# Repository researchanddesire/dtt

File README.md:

# DT Trainer

<p align="center">
  
</p>

<p align="center">
  <a href="https://www.researchanddesire.com/products/deepthroat-trainer"><b>Get the Deepthroat Trainer</b></a><br>
  Black Friday: use code <code>BLACK_FRIDAY_2026</code> at checkout.
</p>

ESP32 firmware and hardware for the V1 (4 MiB) and V2 (16 MiB) DT Trainer.
Firmware: MPL-2.0. Hardware: CERN-OHL-S v2. User guides:
[CC BY-SA 4.0](https://github.com/researchanddesire/simple-docs/blob/main/LICENSE).

## Hardware

- [FreeCAD assembly](hardware/cad/)
- [KiCad PCB](hardware/pcb/kicad-rev4/217A_dttrainer_rev4/)
- [PCB production files](hardware/pcb/production/)
- [Assembly guide](assembly-docs/assembly-guide.mdx)

## Documentation

[User guides](docs/) mirror [Simple Docs](https://github.com/researchanddesire/simple-docs/tree/main/content/dtt).
The daily sync can also run with `python software/scripts/sync_user_docs.py`.
[Firmware and engineering docs](developer-docs/docs/) are maintained here.

## Build

Software lives in [`software/`](software/): the PlatformIO firmware project in
[`software/firmware/`](software/firmware/), development and CI tooling in
[`software/scripts/`](software/scripts/), and local development settings in
[`software/dev/`](software/dev/). Use Python 3.12 and PlatformIO Core 6.2.0:

```sh
python -m pip install platformio==6.2.0
cd software/firmware
pio run -e staging-v1 -e staging-v2 -e production-v1 -e production-v2
```

Select the environment matching the board. Builds do not flash a device.
Development builds (`development`, `development-v1`, `development-v2`) target a
local dashboard on port 3000 (or the origin in the ignored
`software/dev/local.settings.json`). Release builds read the dashboard API credential
from the `RAD_PUBLIC_KEY` environment variable; without it they use the
`DEV_KEY_123` placeholder. Never commit the credential. Flash explicitly:

```sh
pio run -e development-v1 -t upload
```

Keep deployed partition offsets and stored device identity intact.
See [AGENTS.md](AGENTS.md), [software/firmware/README.md](software/firmware/README.md), and
[CI](.github/workflows/) for checks.

See [CONTRIBUTING.md](CONTRIBUTING.md) to contribute.

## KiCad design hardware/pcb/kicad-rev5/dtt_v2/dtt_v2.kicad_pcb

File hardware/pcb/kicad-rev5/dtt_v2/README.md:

# DTT v2 PCB (rev 5)

ESP32-S3 board for the DTT v2: 2.0 in touch screen, VL53L4CD time-of-flight
sensor, LSM6DSO + LIS3MDL 9DOF IMU, side PH6 accessory port. No LEDs, button
or headphone jack. 38 x 64 mm (rev 4 is 44 x 92 mm) with four M2 case-screw
holes. LCSC numbers on every part except the screen connector and the PH6
header. The [case and cradle](../../../cad/dtt-v2/) are built around it.

Status: routed, KiCad 9 DRC clean. Not yet reviewed or fabbed.

| Back | Front |
| --- | --- |
|  |  |

## Source

`build_dtt_v2.py` generates the schematic, libraries, project and placed board
from one netlist; `route_dtt_v2.py` routes it (about an hour). Both overwrite
the board, so once it is hand-edited in KiCad, stop running them.

## PH6 accessory port

| Pin | Signal |
| --- | --- |
| 1 | GND |
| 2 | VSYS (0.5 A PTC) |
| 3 | OUT1, 3.3 V high-side |
| 4 | OUT2, 3.3 V high-side |
| 5 | I2C SDA |
| 6 | I2C SCL |

Existing 3.5 mm accessories use an adapter: tip GND, ring 1 OUT1, ring 2 OUT2.

## I2C addresses

Touch 0x15, ToF 0x29, IMU 0x6A, magnetometer 0x1C.

## Screen

Bare 2.0 in 240x320 IPS panel with CST816D touch, the one inside Waveshare's
"2inch Capacitive Touch LCD" module. 21-pin 0.5 mm FPC, pin order from that
module's schematic:

| Pin | Signal | | Pin | Signal |
| --- | --- | --- | --- | --- |
| 1 | GND | | 12 | RS (DC) |
| 2 | LEDK | | 13 | CS |
| 3 | LEDA | | 14 | GND |
| 4 | GND | | 15 | TP_VDD (3.3 V) |
| 5, 6 | VCC (3.3 V) | | 16 | TP_RESET |
| 7 | GND | | 17 | TP_INT |
| 8 | RESET | | 18 | TP_SDA |
| 9 | SCL (SPI clock) | | 19 | TP_SCL |
| 10 | TE | | 20, 21 | GND |
| 11 | SDA (MOSI) | | | |

## Open items

- Check on a panel sample: LEDA/LEDK order, FPC contact side (J3 is
  top-contact for now), glass outline (36 x 52 mm assumed).
- Backlight is 3.3 V through 10 R, so not full brightness.
- Battery: 702035 (400 mAh). R3 is 3.3k, so the TP4054 charges at about 300 mA (0.76C).
- SW1 reuses the rev 4 footprint with its tight locating holes.
- J4 is the surface-mount S6B-PH-SM4-TB (no pins through the front under the
  glass); confirm its LCSC number before ordering.
- The ToF sits at the bottom right of the front face, beside the screen FPC,
  looking through a window in the case bezel.

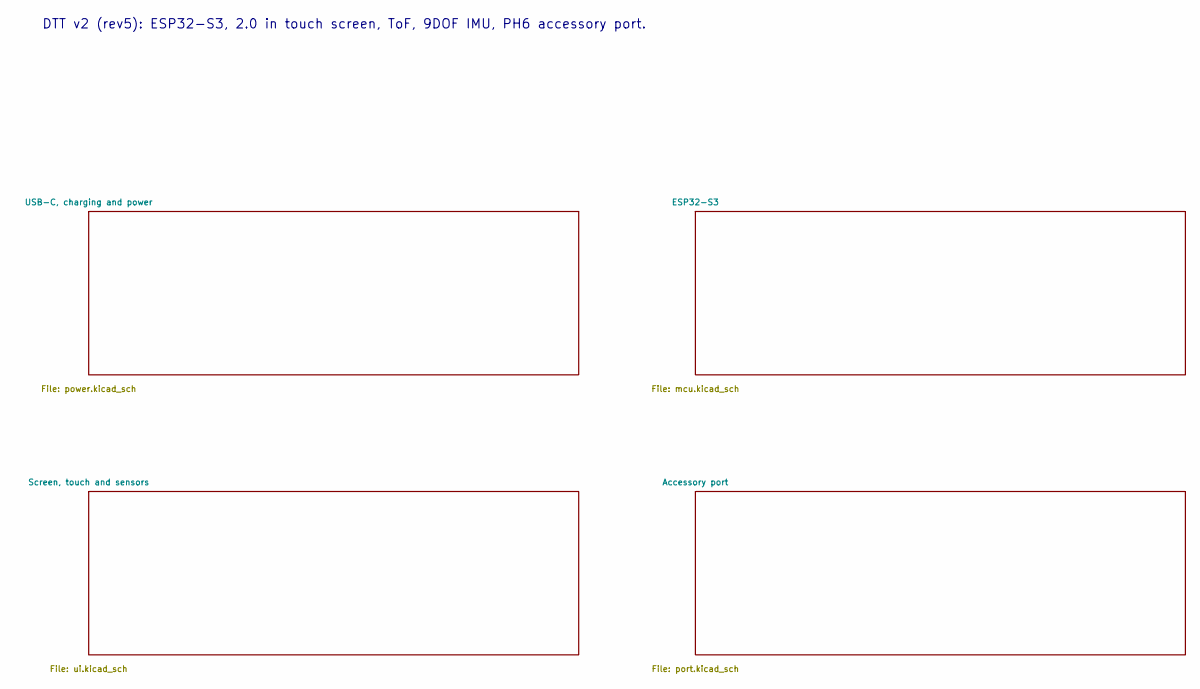
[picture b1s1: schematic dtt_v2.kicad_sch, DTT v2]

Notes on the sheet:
DTT v2 (rev5): ESP32-S3, 2.0 in touch screen, ToF, 9DOF IMU, PH6 accessory port.

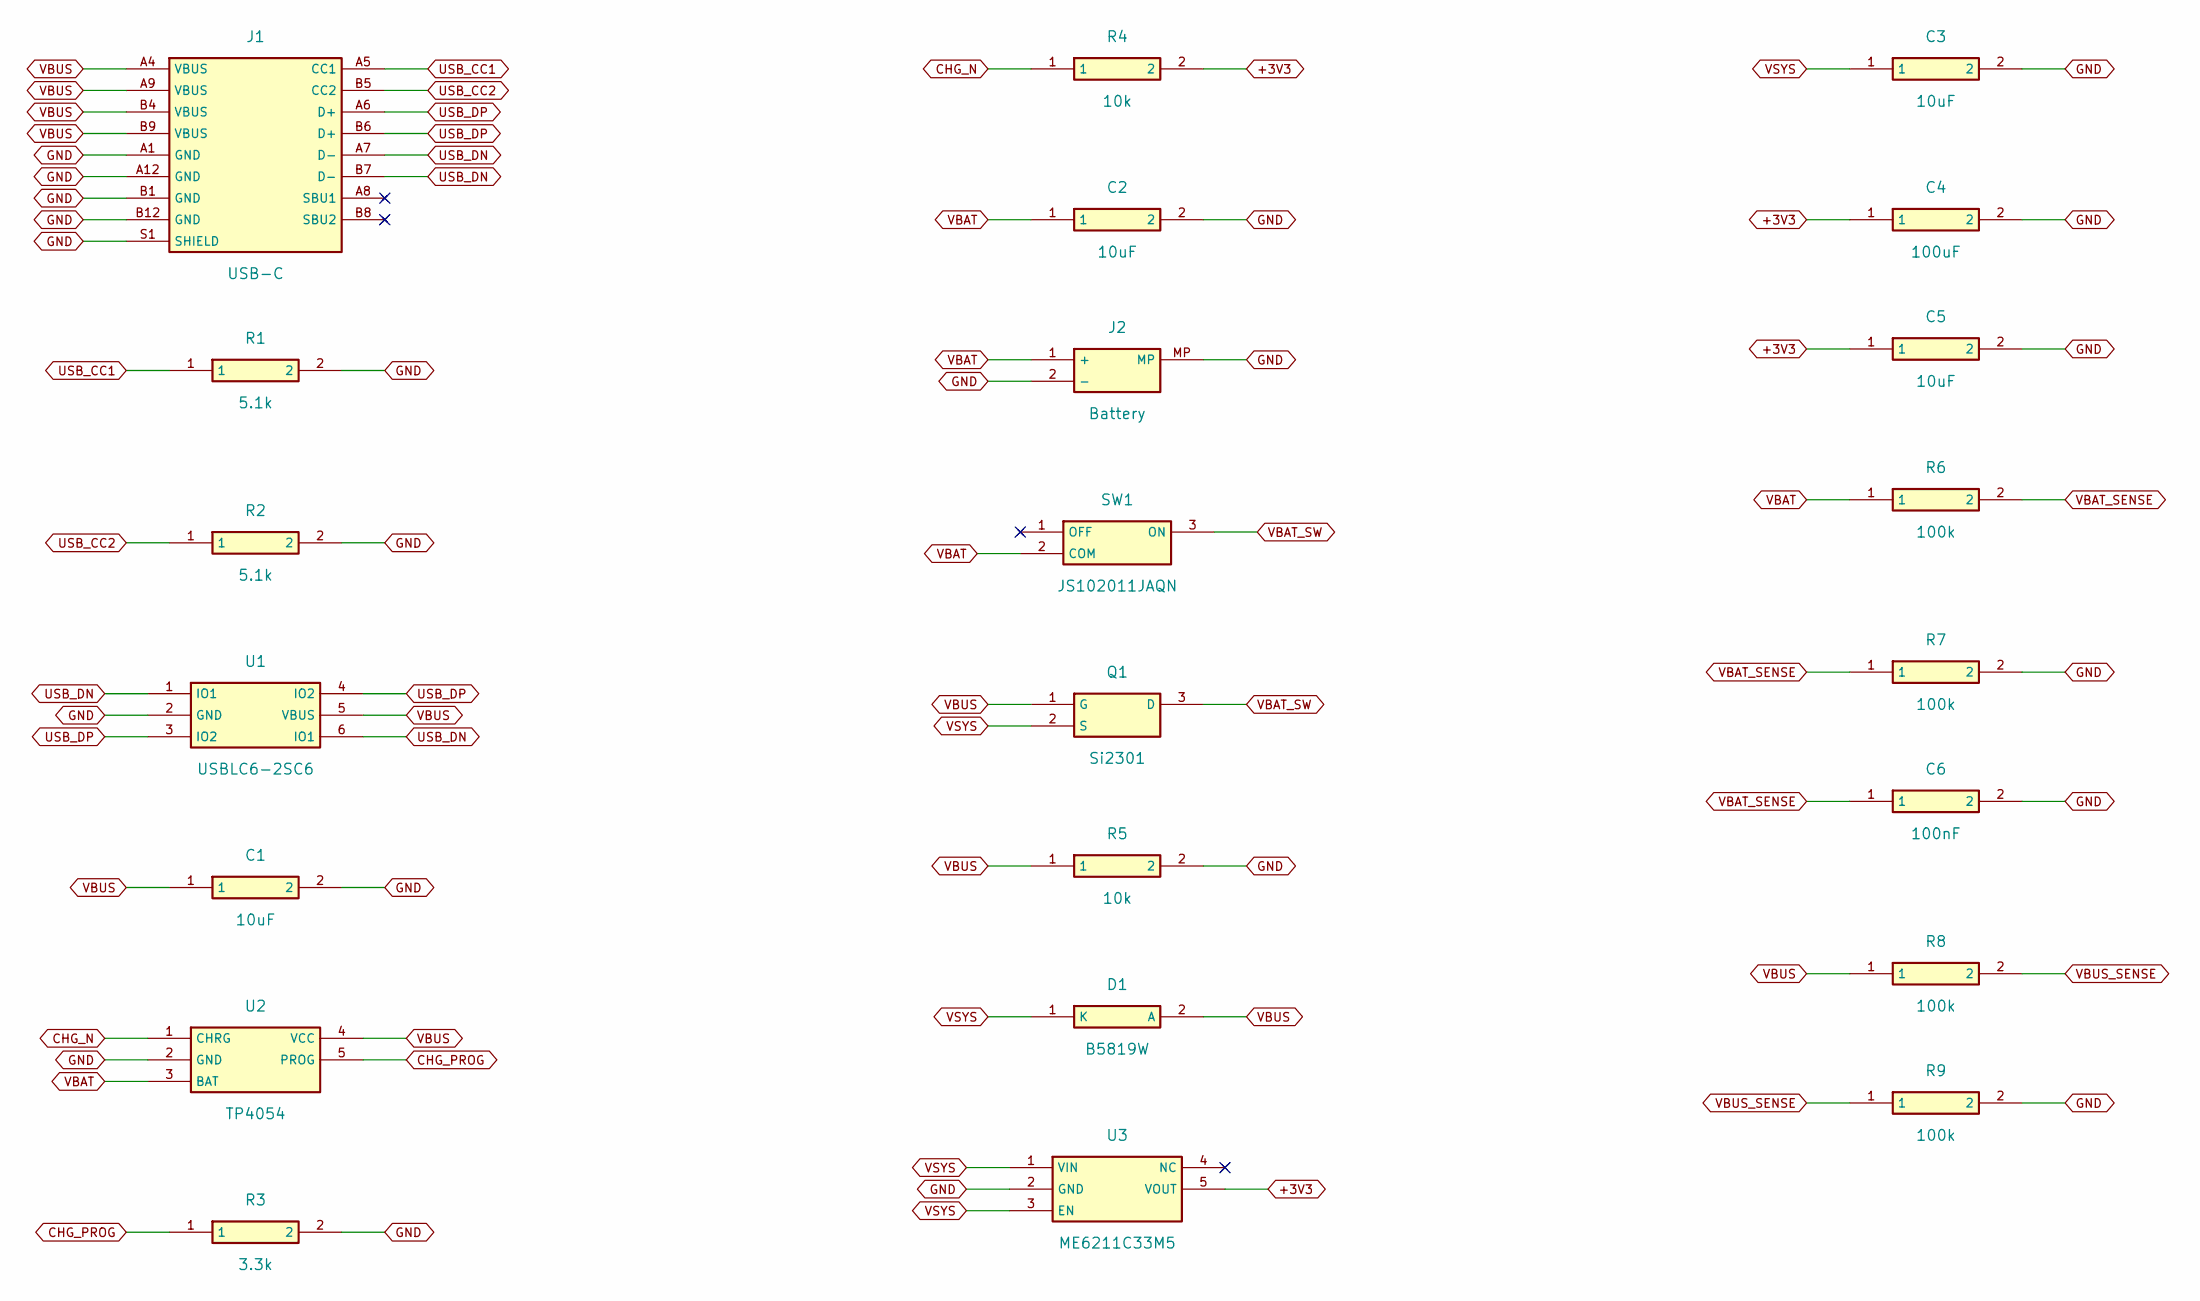
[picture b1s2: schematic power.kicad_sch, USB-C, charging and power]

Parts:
C1, C2, C3, C5: 10uF; C_0805_2012Metric; LCSC C89827
C4: 100uF; C_1206_3216Metric; LCSC C7432784
C6: 100nF; C_0402_1005Metric; LCSC C56392
D1: B5819W; D_SOD-123; LCSC C22463588
J1: USB-C; USB_C_Receptacle_HRO_TYPE-C-31-M-12; LCSC C165948
J2: Battery; JST_PH_S2B-PH-SM4-TB_1x02-1MP_P2.00mm_Horizontal; LCSC C295747
Q1: Si2301; SOT-23; LCSC C727151
R1, R2: 5.1k; R_0402_1005Metric; LCSC C25905
R3: 3.3k; R_0402_1005Metric; LCSC C25890
R4, R5: 10k; R_0402_1005Metric; LCSC C25744
R6, R7, R8, R9: 100k; R_0402_1005Metric; LCSC C25741
SW1: JS102011JAQN; SW_SPDT_JS102011JAQN; LCSC C221658
U1: USBLC6-2SC6; SOT-23-6; LCSC C7519
U2: TP4054; SOT-23-5; LCSC C32574
U3: ME6211C33M5; SOT-23-5; LCSC C82942

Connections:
+3V3: C4.1, C5.1, R4.2, U3.5 (VOUT); also elsewhere on the board
CHG_N: R4.1, U2.1 (CHRG); also elsewhere on the board
CHG_PROG: R3.1, U2.5 (PROG)
GND: C1.2, C2.2, C3.2, C4.2, C5.2, C6.2, J1.A1 (GND), J1.A12 (GND), J1.B1 (GND), J1.B12 (GND), J1.S1 (SHIELD), J2.2 (-), J2.MP, R1.2, R2.2, R3.2, R5.2, R7.2, R9.2, U1.2 (GND), U2.2 (GND), U3.2 (GND); also elsewhere on the board
USB_CC1: J1.A5 (CC1), R1.1
USB_CC2: J1.B5 (CC2), R2.1
USB_DN: J1.A7 (D-), J1.B7 (D-), U1.1 (IO1), U1.6 (IO1); also elsewhere on the board
USB_DP: J1.A6 (D+), J1.B6 (D+), U1.3 (IO2), U1.4 (IO2); also elsewhere on the board
VBAT: C2.1, J2.1 (+), R6.1, SW1.2 (COM), U2.3 (BAT)
VBAT_SENSE: C6.1, R6.2, R7.1; also elsewhere on the board
VBAT_SW: Q1.3 (D), SW1.3 (ON)
VBUS: C1.1, D1.2 (A), J1.A4 (VBUS), J1.A9 (VBUS), J1.B4 (VBUS), J1.B9 (VBUS), Q1.1 (G), R5.1, R8.1, U1.5 (VBUS), U2.4 (VCC)
VBUS_SENSE: R8.2, R9.1; also elsewhere on the board
VSYS: C3.1, D1.1 (K), Q1.2 (S), U3.1 (VIN), U3.3 (EN); also elsewhere on the board

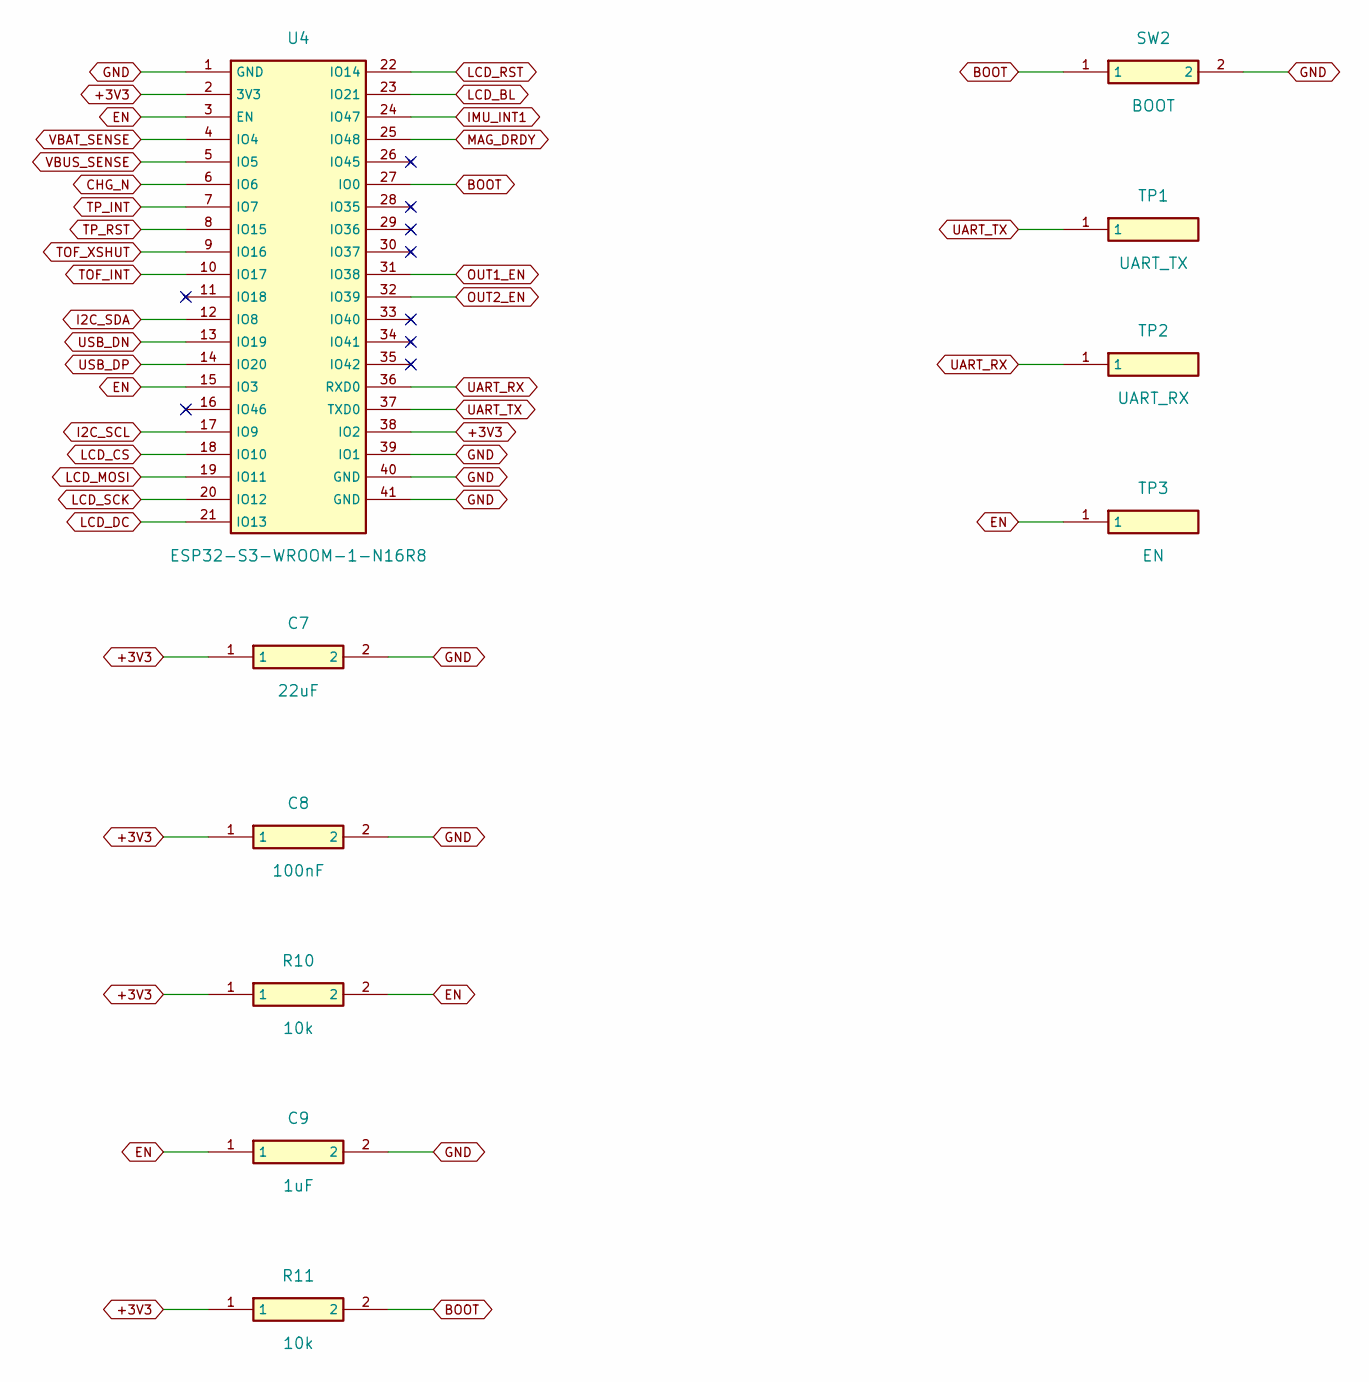
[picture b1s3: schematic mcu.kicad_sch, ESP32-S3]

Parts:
C7: 22uF; C_0805_2012Metric; LCSC TBD
C8: 100nF; C_0402_1005Metric; LCSC C56392
C9: 1uF; C_0402_1005Metric; LCSC C52923
R10, R11: 10k; R_0402_1005Metric; LCSC C25744
SW2: BOOT; SW_Push_1P1T_XKB_TS-1187A; LCSC TBD
TP1: UART_TX; TestPoint_Pad_1.0mm; LCSC TBD
TP2: UART_RX; TestPoint_Pad_1.0mm; LCSC TBD
TP3: EN; TestPoint_Pad_1.0mm; LCSC TBD
U4: ESP32-S3-WROOM-1-N16R8; ESP32-S3-WROOM-1; LCSC C2913202

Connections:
+3V3: C7.1, C8.1, R10.1, R11.1, U4.2 (3V3), U4.38 (IO2); also elsewhere on the board
BOOT: R11.2, SW2.1, U4.27 (IO0)
CHG_N: U4.6 (IO6); also elsewhere on the board
EN: C9.1, R10.2, TP3.1, U4.3 (EN), U4.15 (IO3)
GND: C7.2, C8.2, C9.2, SW2.2, U4.1 (GND), U4.39 (IO1), U4.40 (GND), U4.41 (GND); also elsewhere on the board
I2C_SCL: U4.17 (IO9); also elsewhere on the board
I2C_SDA: U4.12 (IO8); also elsewhere on the board
IMU_INT1: U4.24 (IO47); also elsewhere on the board
LCD_BL: U4.23 (IO21); also elsewhere on the board
LCD_CS: U4.18 (IO10); also elsewhere on the board
LCD_DC: U4.21 (IO13); also elsewhere on the board
LCD_MOSI: U4.19 (IO11); also elsewhere on the board
LCD_RST: U4.22 (IO14); also elsewhere on the board
LCD_SCK: U4.20 (IO12); also elsewhere on the board
LCD_TE: U4.33 (IO40); also elsewhere on the board
MAG_DRDY: U4.25 (IO48); also elsewhere on the board
OUT1_EN: U4.31 (IO38); also elsewhere on the board
OUT2_EN: U4.32 (IO39); also elsewhere on the board
TOF_INT: U4.10 (IO17); also elsewhere on the board
TOF_XSHUT: U4.9 (IO16); also elsewhere on the board
TP_INT: U4.7 (IO7); also elsewhere on the board
TP_RST: U4.8 (IO15); also elsewhere on the board
UART_RX: TP2.1, U4.36 (RXD0)
UART_TX: TP1.1, U4.37 (TXD0)
USB_DN: U4.13 (IO19); also elsewhere on the board
USB_DP: U4.14 (IO20); also elsewhere on the board
VBAT_SENSE: U4.4 (IO4); also elsewhere on the board
VBUS_SENSE: U4.5 (IO5); also elsewhere on the board

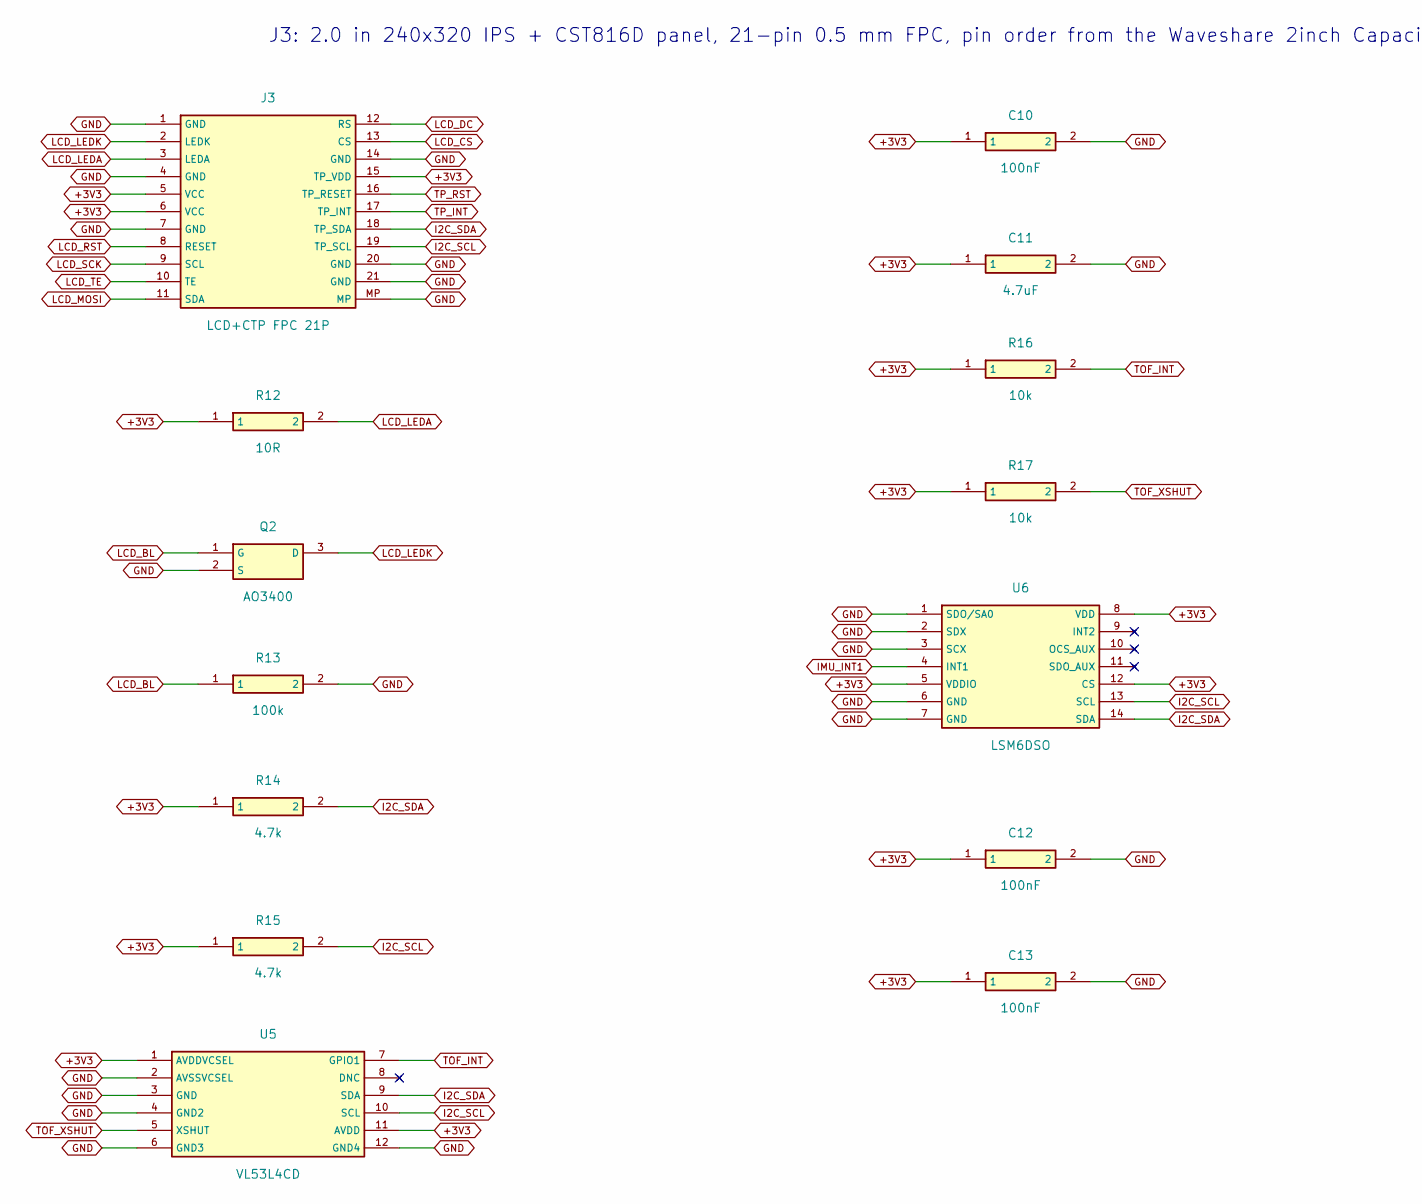
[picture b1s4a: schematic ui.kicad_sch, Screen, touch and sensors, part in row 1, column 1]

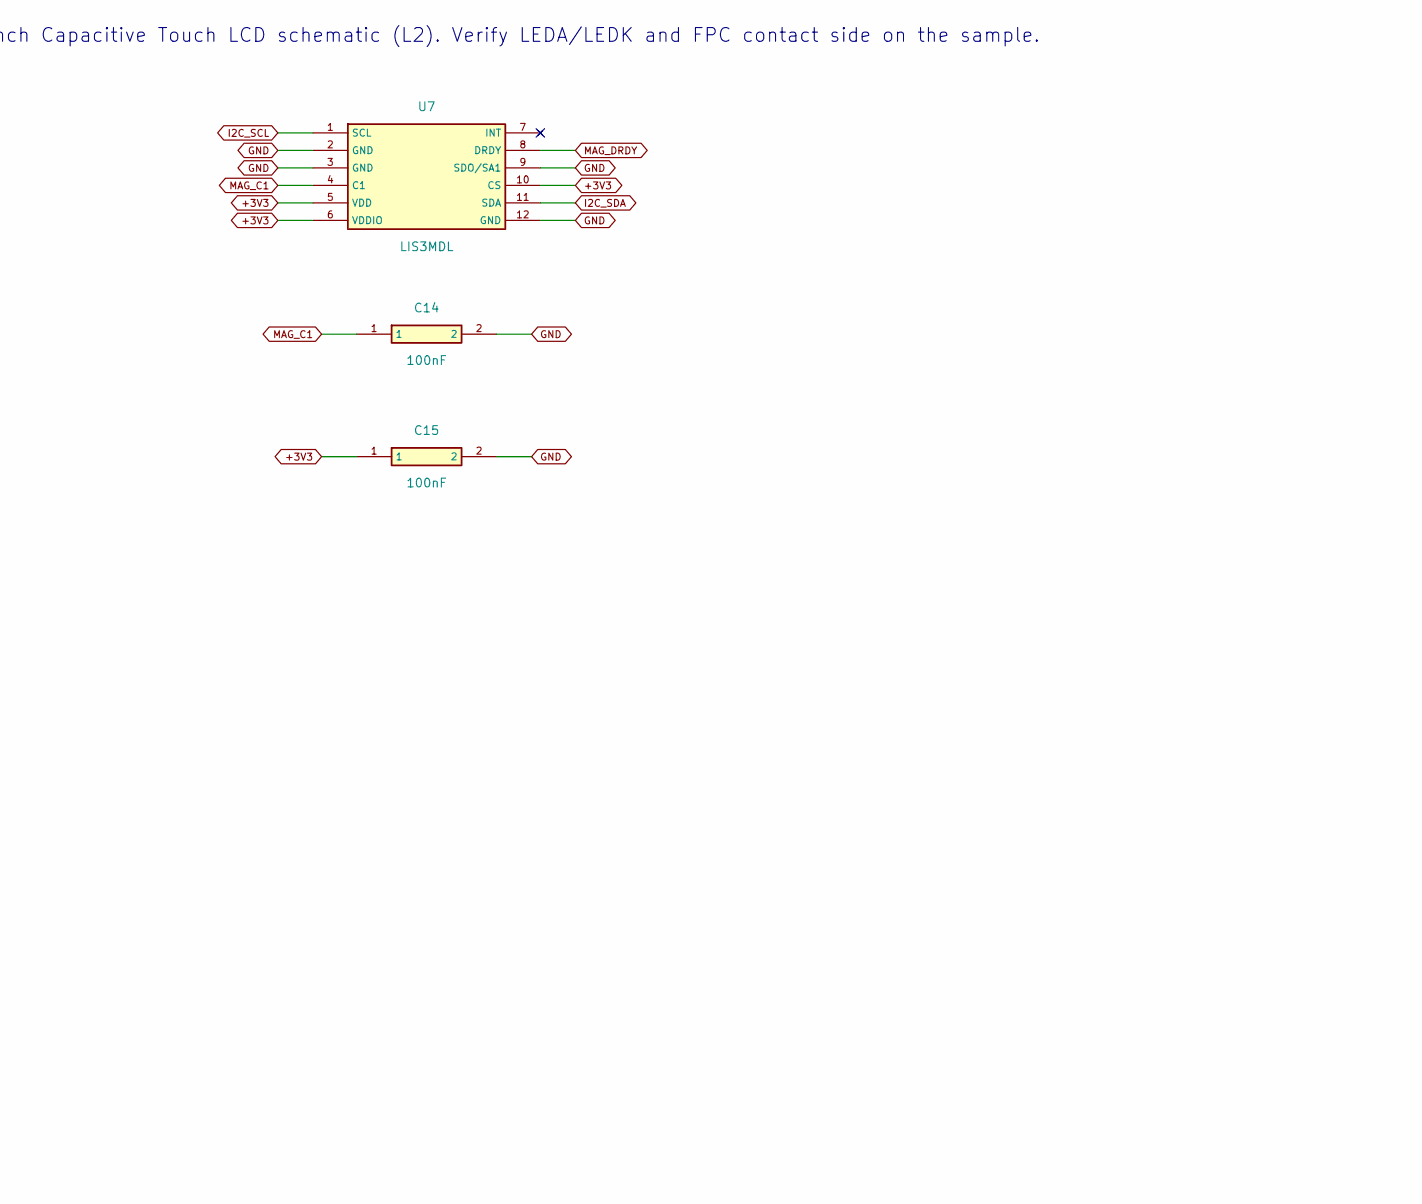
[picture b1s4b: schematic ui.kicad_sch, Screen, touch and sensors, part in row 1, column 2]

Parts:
C10, C12, C13, C14, C15: 100nF; C_0402_1005Metric; LCSC C56392
C11: 4.7uF; C_0402_1005Metric; LCSC C23733
J3: LCD+CTP FPC 21P; TE_2-1734839-1_1x21-1MP_P0.5mm_Horizontal; LCSC TBD
Q2: AO3400; SOT-23; LCSC C2938367
R12: 10R; R_0402_1005Metric; LCSC C25077
R13: 100k; R_0402_1005Metric; LCSC C25741
R14, R15: 4.7k; R_0402_1005Metric; LCSC C25900
R16, R17: 10k; R_0402_1005Metric; LCSC C25744
U5: VL53L4CD; ST_VL53L4CD_LGA-12_4.4x2.4mm; LCSC C3178291
U6: LSM6DSO; ST_LGA-14_2.5x3mm_P0.5mm; LCSC C2655100
U7: LIS3MDL; ST_LGA-12_2x2mm_P0.5mm; LCSC C478483

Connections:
+3V3: C10.1, C11.1, C12.1, C13.1, C15.1, J3.5 (VCC), J3.6 (VCC), J3.15 (TP_VDD), R12.1, R14.1, R15.1, R16.1, R17.1, U5.1 (AVDDVCSEL), U5.11 (AVDD), U6.5 (VDDIO), U6.8 (VDD), U6.12 (CS), U7.5 (VDD), U7.6 (VDDIO), U7.10 (CS); also elsewhere on the board
GND: C10.2, C11.2, C12.2, C13.2, C14.2, C15.2, J3.1 (GND), J3.4 (GND), J3.7 (GND), J3.14 (GND), J3.20 (GND), J3.21 (GND), J3.MP, Q2.2 (S), R13.2, U5.2 (AVSSVCSEL), U5.3 (GND), U5.4 (GND2), U5.6 (GND3), U5.12 (GND4), U6.1 (SDO/SA0), U6.2 (SDX), U6.3 (SCX), U6.6 (GND), U6.7 (GND), U7.2 (GND), U7.3 (GND), U7.9 (SDO/SA1), U7.12 (GND); also elsewhere on the board
I2C_SCL: J3.19 (TP_SCL), R15.2, U5.10 (SCL), U6.13 (SCL), U7.1 (SCL); also elsewhere on the board
I2C_SDA: J3.18 (TP_SDA), R14.2, U5.9 (SDA), U6.14 (SDA), U7.11 (SDA); also elsewhere on the board
IMU_INT1: U6.4 (INT1); also elsewhere on the board
LCD_BL: Q2.1 (G), R13.1; also elsewhere on the board
LCD_CS: J3.13 (CS); also elsewhere on the board
LCD_DC: J3.12 (RS); also elsewhere on the board
LCD_LEDA: J3.3 (LEDA), R12.2
LCD_LEDK: J3.2 (LEDK), Q2.3 (D)
LCD_MOSI: J3.11 (SDA); also elsewhere on the board
LCD_RST: J3.8 (RESET); also elsewhere on the board
LCD_SCK: J3.9 (SCL); also elsewhere on the board
LCD_TE: J3.10 (TE); also elsewhere on the board
MAG_C1: C14.1, U7.4 (C1)
MAG_DRDY: U7.8 (DRDY); also elsewhere on the board
TOF_INT: R16.2, U5.7 (GPIO1); also elsewhere on the board
TOF_XSHUT: R17.2, U5.5 (XSHUT); also elsewhere on the board
TP_INT: J3.17 (TP_INT); also elsewhere on the board
TP_RST: J3.16 (TP_RESET); also elsewhere on the board

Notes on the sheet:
J3: 2.0 in 240x320 IPS + CST816D panel, 21-pin 0.5 mm FPC, pin order from the Waveshare 2inch Capacitive Touch LCD schematic (L2). Verify LEDA/LEDK and FPC contact side on the sample.

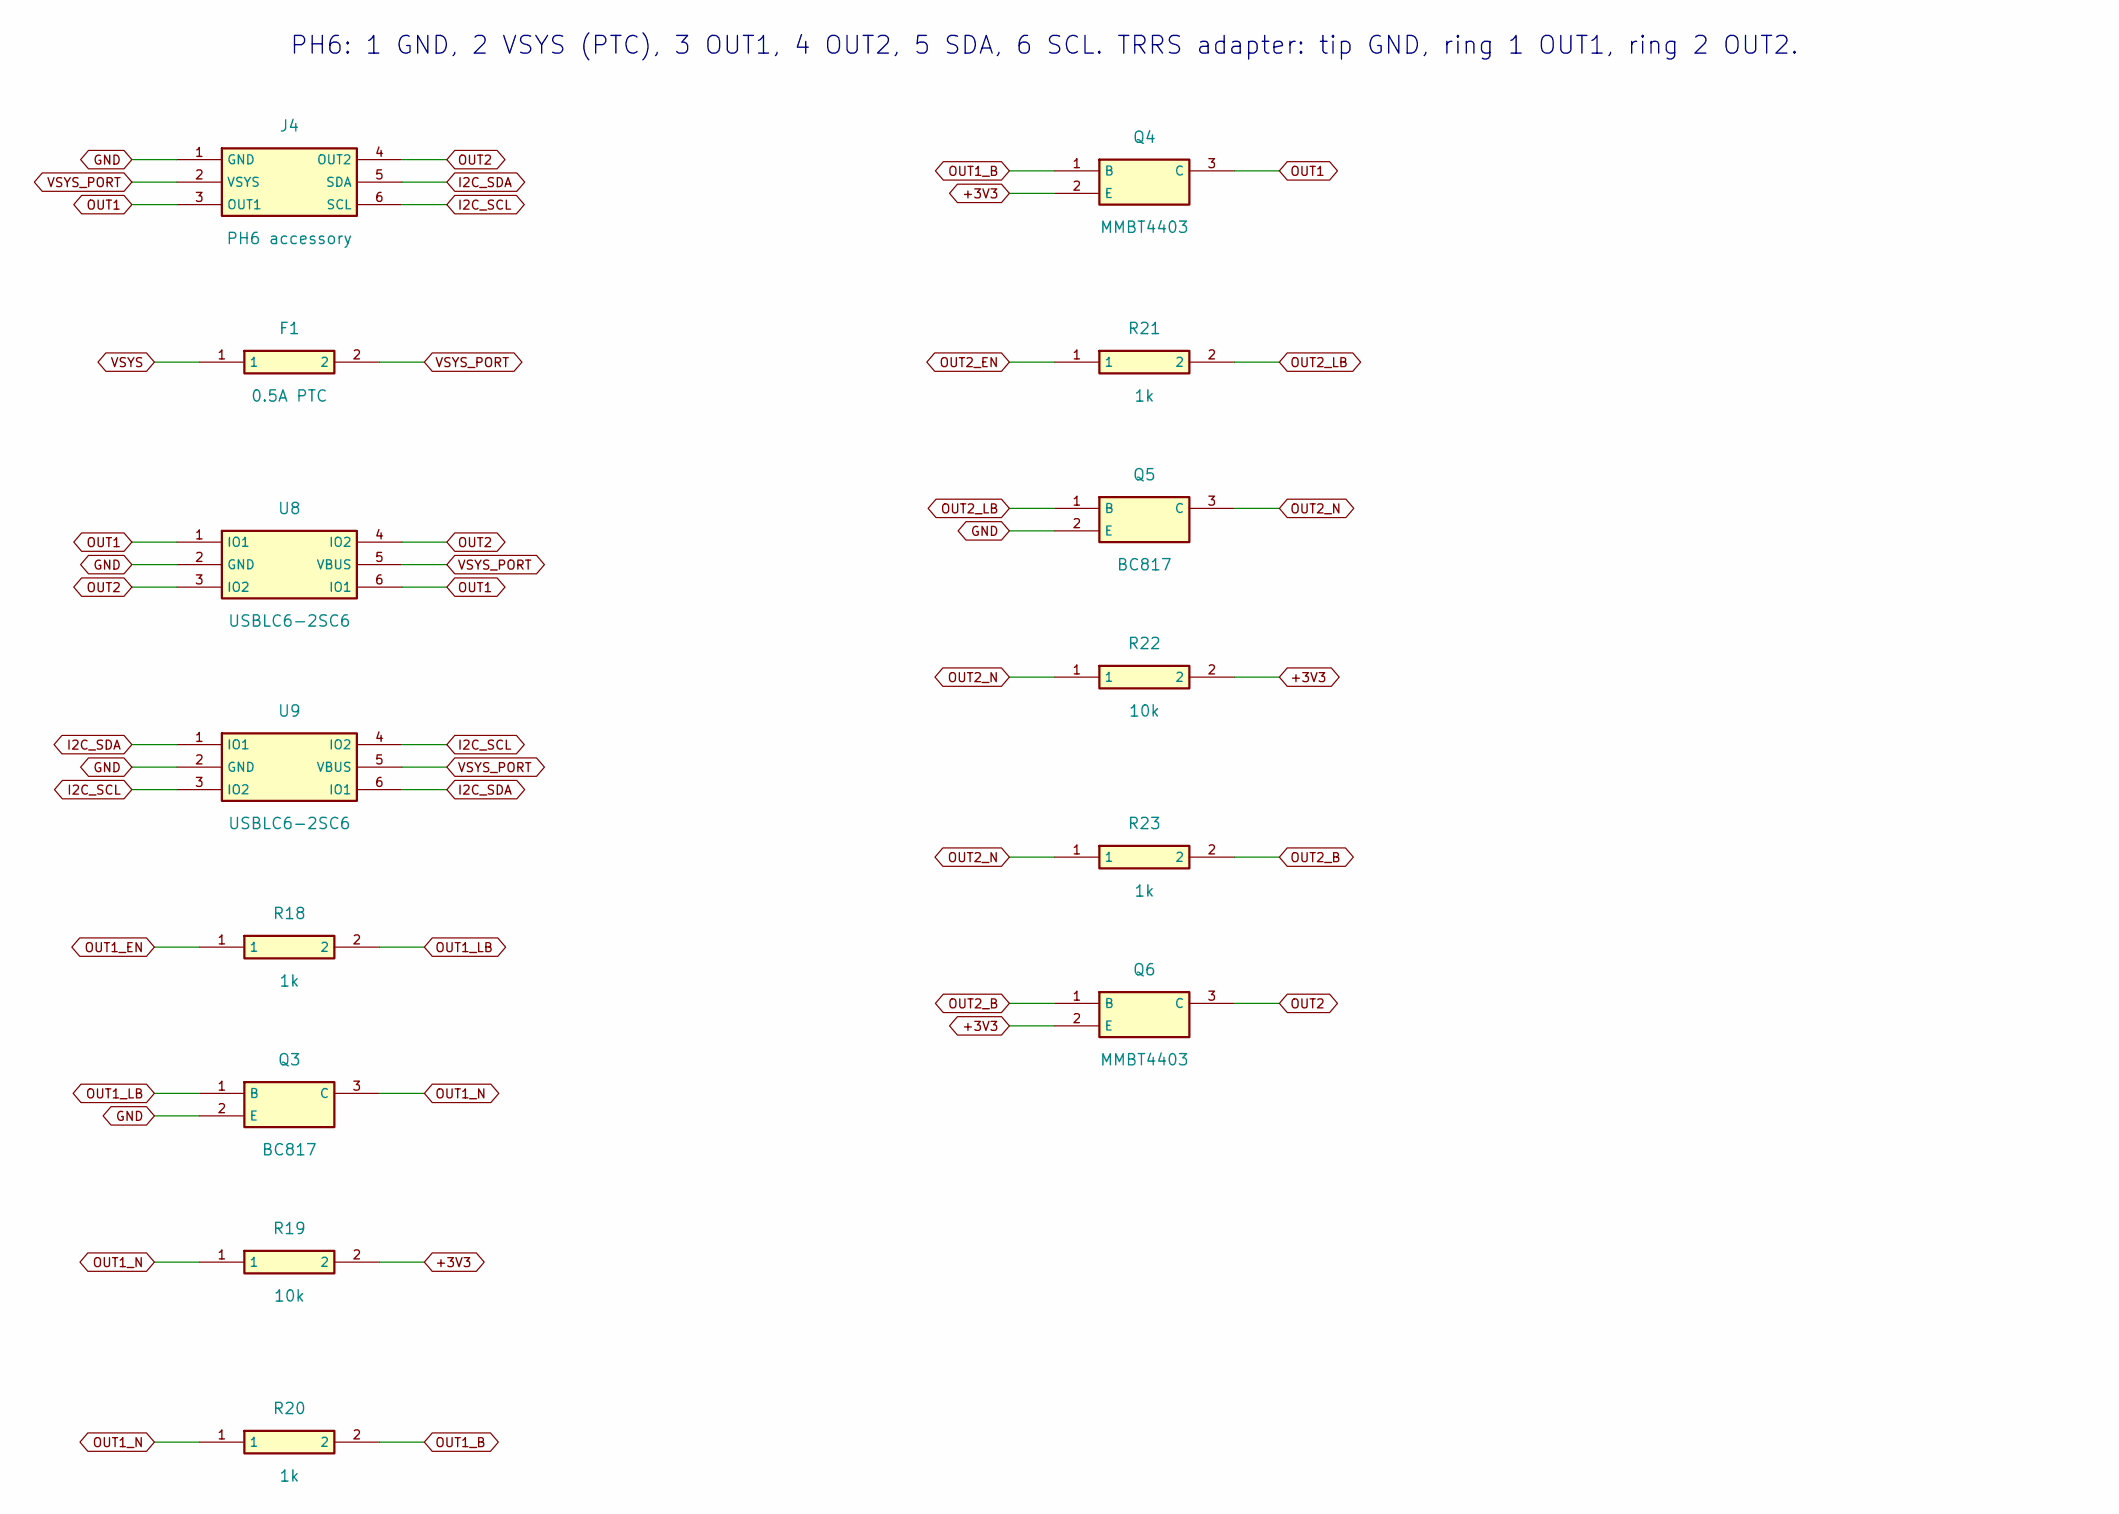
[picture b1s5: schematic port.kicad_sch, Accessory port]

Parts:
F1: 0.5A PTC; Fuse_0805_2012Metric; LCSC C269104
J4: PH6 accessory; JST_PH_S6B-PH-K_1x06_P2.00mm_Horizontal; LCSC C157920
Q3, Q5: BC817; SOT-23; LCSC C8658
Q4, Q6: MMBT4403; SOT-23; LCSC C78864
R18, R20, R21, R23: 1k; R_0402_1005Metric; LCSC C11702
R19, R22: 10k; R_0402_1005Metric; LCSC C25744
U8, U9: USBLC6-2SC6; SOT-23-6; LCSC C7519

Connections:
+3V3: Q4.2 (E), Q6.2 (E), R19.2, R22.2; also elsewhere on the board
GND: J4.1 (GND), Q3.2 (E), Q5.2 (E), U8.2 (GND), U9.2 (GND); also elsewhere on the board
I2C_SCL: J4.6 (SCL), U9.3 (IO2), U9.4 (IO2); also elsewhere on the board
I2C_SDA: J4.5 (SDA), U9.1 (IO1), U9.6 (IO1); also elsewhere on the board
OUT1: J4.3 (OUT1), Q4.3 (C), U8.1 (IO1), U8.6 (IO1)
OUT1_B: Q4.1 (B), R20.2
OUT1_EN: R18.1; also elsewhere on the board
OUT1_LB: Q3.1 (B), R18.2
OUT1_N: Q3.3 (C), R19.1, R20.1
OUT2: J4.4 (OUT2), Q6.3 (C), U8.3 (IO2), U8.4 (IO2)
OUT2_B: Q6.1 (B), R23.2
OUT2_EN: R21.1; also elsewhere on the board
OUT2_LB: Q5.1 (B), R21.2
OUT2_N: Q5.3 (C), R22.1, R23.1
VSYS: F1.1; also elsewhere on the board
VSYS_PORT: F1.2, J4.2 (VSYS), U8.5 (VBUS), U9.5 (VBUS)

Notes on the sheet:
PH6: 1 GND, 2 VSYS (PTC), 3 OUT1, 4 OUT2, 5 SDA, 6 SCL. TRRS adapter: tip GND, ring 1 OUT1, ring 2 OUT2.

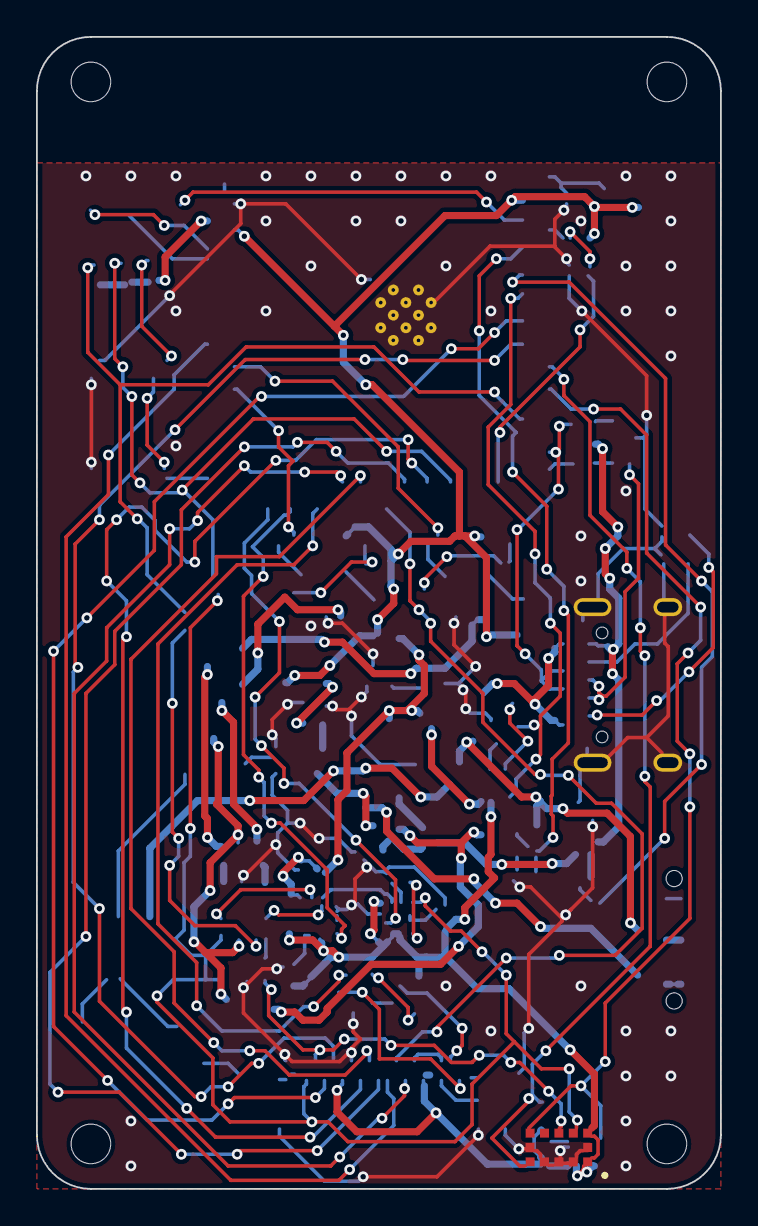
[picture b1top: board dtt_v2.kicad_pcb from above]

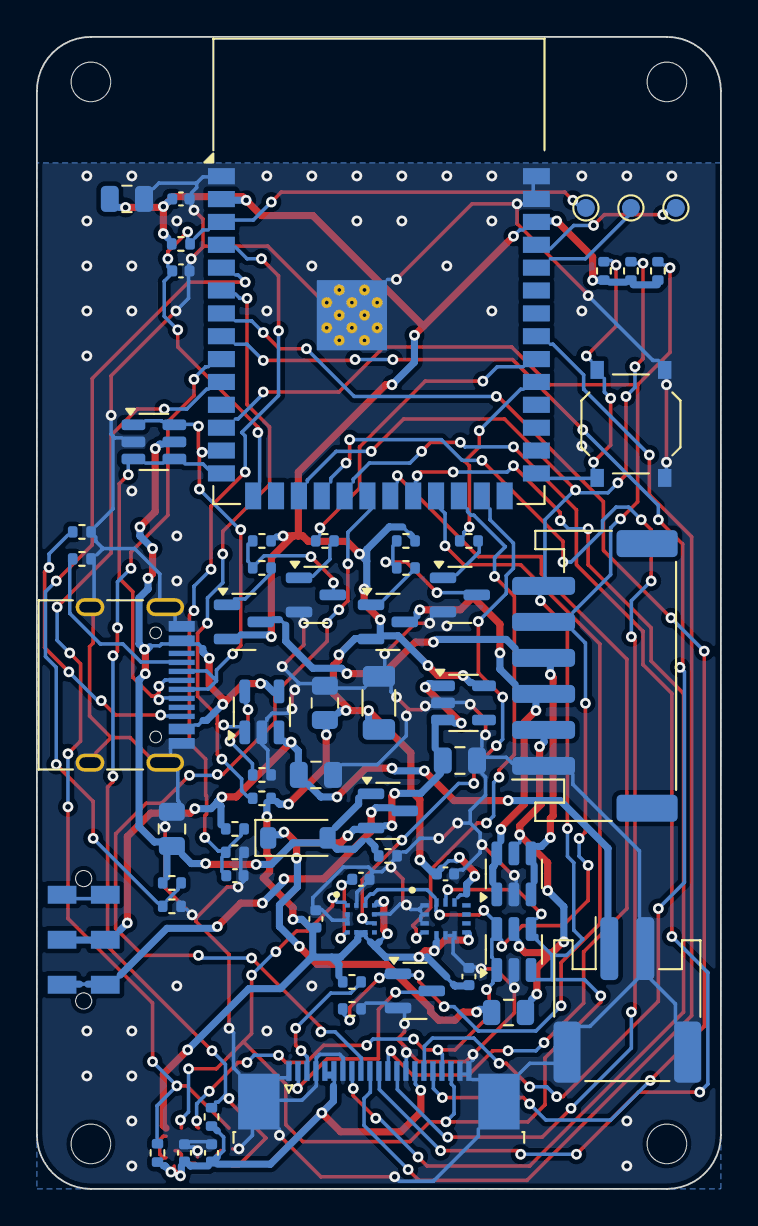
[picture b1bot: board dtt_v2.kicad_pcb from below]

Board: 2 copper layers, 38.0 x 64.0 mm, 68 parts (63 on the bottom side), 47 nets.

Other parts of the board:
H1, H2, H3, H4: M2 case screw; MountingHole_2.2mm_M2

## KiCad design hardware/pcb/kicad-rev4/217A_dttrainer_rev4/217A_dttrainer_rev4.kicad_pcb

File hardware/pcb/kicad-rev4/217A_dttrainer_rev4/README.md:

# DTT rev4 PCB

Open `217A_dttrainer_rev4.kicad_pro` in KiCad 7+. The project includes a six-sheet
schematic and local libraries. See [DESIGN.md](DESIGN.md) for layout notes.

[Production files](../../production/) include Gerbers, drills, BOMs, placement,
and schematic PDF. Regenerate them and the KiCanvas preview with:

```sh
python export_production.py
```

CI runs `python export_production.py --check` to catch stale exports.

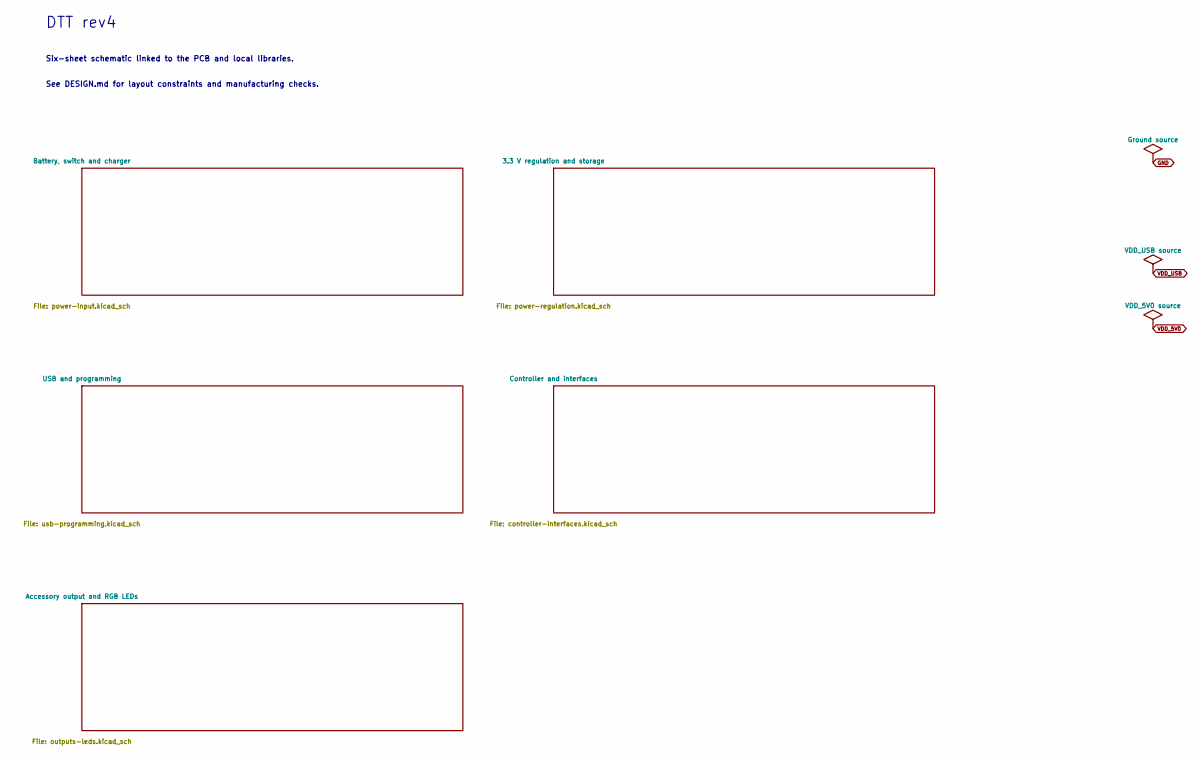
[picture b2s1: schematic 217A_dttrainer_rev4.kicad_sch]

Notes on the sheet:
DTT rev4
Six-sheet schematic linked to the PCB and local libraries.
See DESIGN.md for layout constraints and manufacturing checks.

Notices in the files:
hardware/pcb/kicad-rev4/217A_dttrainer_rev4/217A_dttrainer_rev4.kicad_pcb:
CERN-OHL-S v2; manufacturing outputs: hardware/pcb/production
